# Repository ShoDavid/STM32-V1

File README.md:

# **STM32 - KANA 01**
PCB design using the STM32F103, with SWD programming ports, I2C and UART ports, reset and boot button. With USB port for power and communication.
All master files and manufacturing files you can find in this repository, the idea of this PCB is the result of the tutorial available on Youtube of Phil's Lab (https://www.youtube.com/watch?v=aVUqaB0IMh4)

# Manufacturing
I sent it to manufacture using JLCPCB, I'm using this configuration:

# BOM Using InteractiveHtmlBom 

# After manufacture

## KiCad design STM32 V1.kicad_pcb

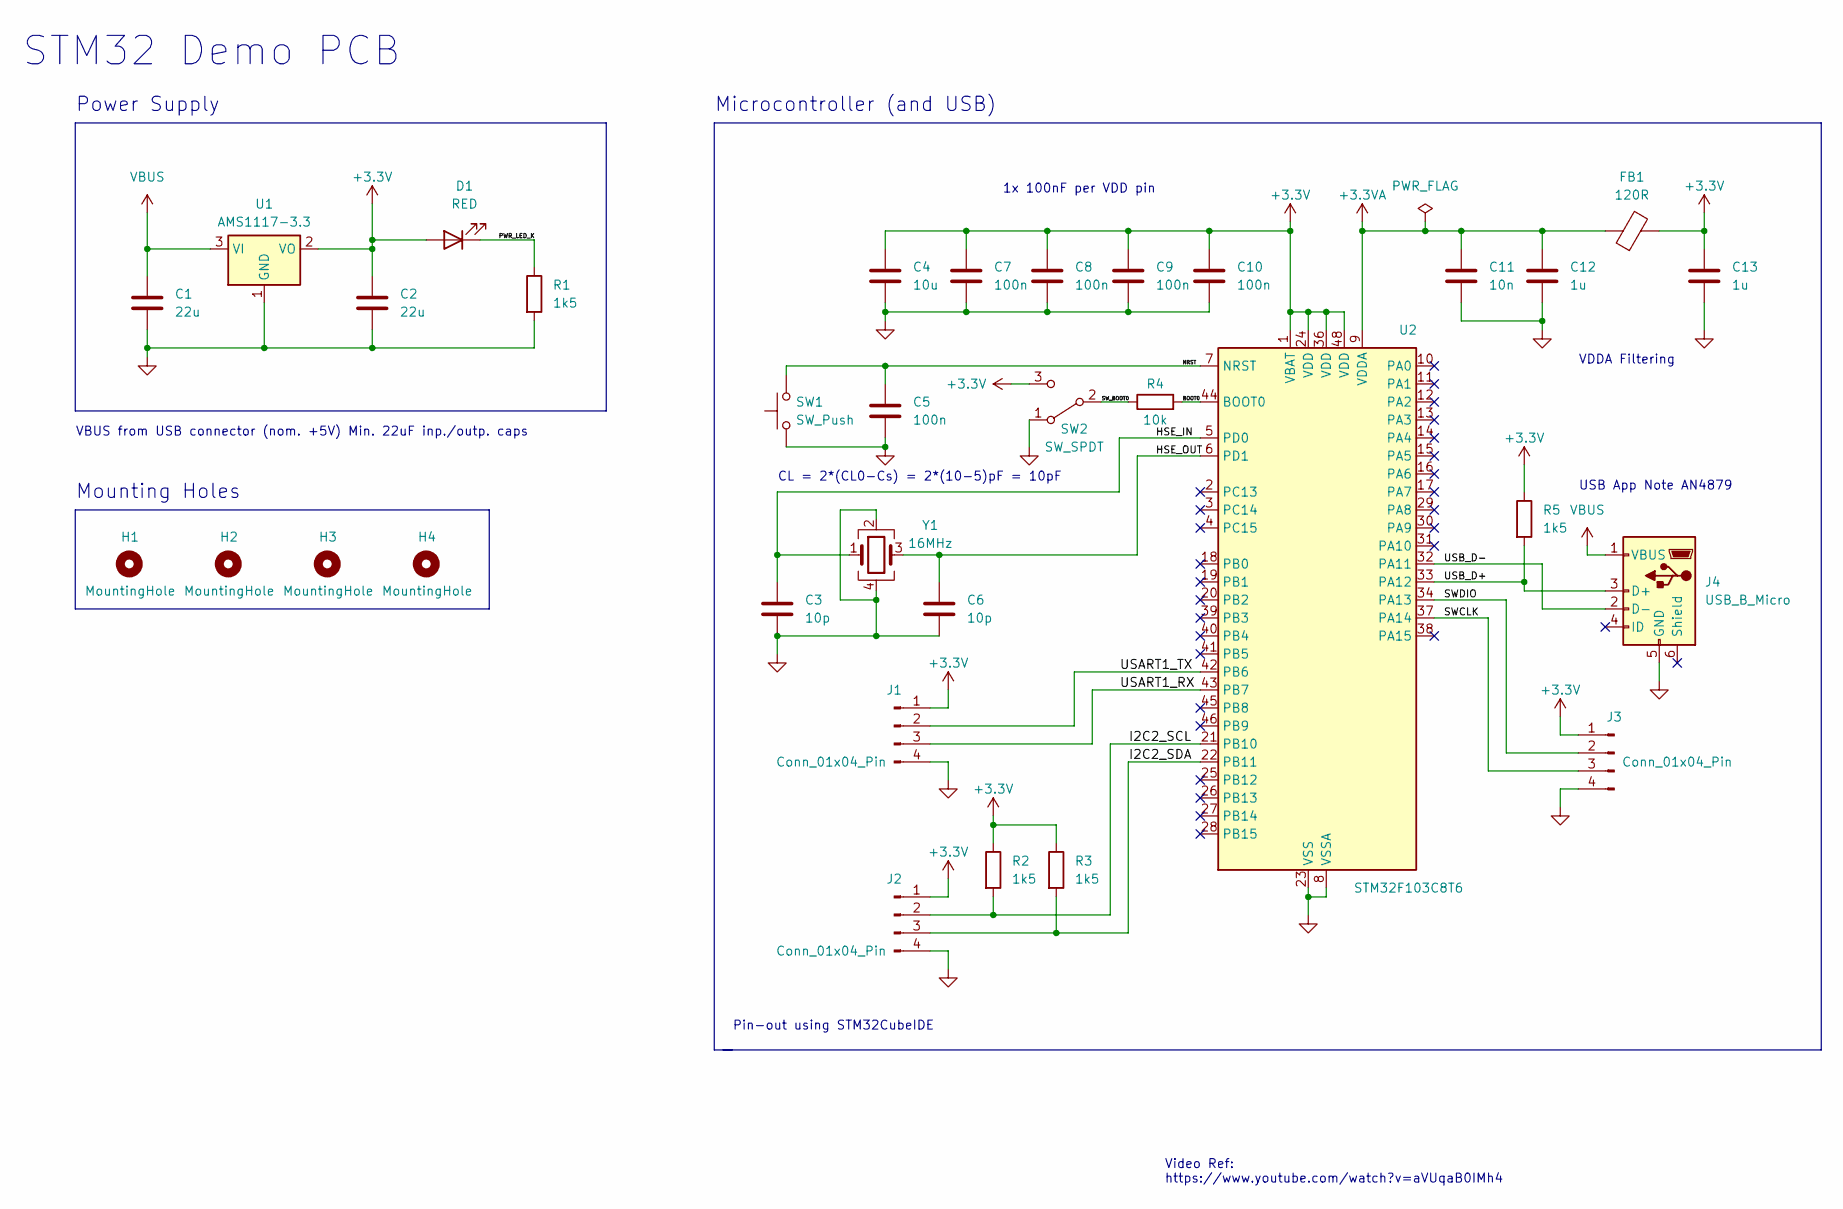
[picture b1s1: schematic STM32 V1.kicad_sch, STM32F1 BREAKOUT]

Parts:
C1, C2: 22u; C_0805_2012Metric
C3, C6: 10p; C_0402_1005Metric
C4: 10u; C_0603_1608Metric
C5, C7, C8, C9, C10: 100n; C_0402_1005Metric
C11: 10n; C_0402_1005Metric
C12, C13: 1u; C_0402_1005Metric
D1: RED; LED_0603_1608Metric
FB1: 120R; L_0603_1608Metric
H1, H2, H3, H4: MountingHole; MountingHole_2.2mm_M2
J1, J2, J3: Conn_01x04_Pin; PinHeader_1x04_P2.54mm_Vertical
J4: USB_B_Micro; USB_Micro-B_Wuerth_629105150521
R1, R2, R3, R5: 1k5; R_0402_1005Metric
R4: 10k; R_0402_1005Metric
SW1: SW_Push; SW_SPST_PTS645
SW2: SW_SPDT; SW_SPDT_PCM12
U1: AMS1117-3.3; SOT-223-3_TabPin2
U2: STM32F103C8T6; LQFP-48_7x7mm_P0.5mm
Y1: 16MHz; Crystal_SMD_3225-4Pin_3.2x2.5mm

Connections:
+3.3V: C2.1, C4.1, C7.1, C8.1, C9.1, C10.1, C13.1, D1.2 (A), FB1.2, J1.1, J2.1, J3.1, R2.1, R3.1, R5.1, SW2.3 (C), U1.2 (VO), U2.1 (VBAT), U2.24 (VDD), U2.36 (VDD), U2.48 (VDD)
+3.3VA: C11.1, C12.1, FB1.1, U2.9 (VDDA)
/BOOT0: R4.2, U2.44 (BOOT0)
/HSE_IN: C3.1, U2.5 (PD0), Y1.1
/HSE_OUT: C6.1, U2.6 (PD1), Y1.3
/I2C2_SCL: J2.2, R2.2, U2.21 (PB10)
/I2C2_SDA: J2.3, R3.2, U2.22 (PB11)
/NRST: C5.1, SW1.2, U2.7 (NRST)
/PWR_LED_K: D1.1 (K), R1.1
/SWCLK: J3.3, U2.37 (PA14)
/SWDIO: J3.2, U2.34 (PA13)
/SW_BOOT0: R4.1, SW2.2 (B)
/USART1_RX: J1.3, U2.43 (PB7)
/USART1_TX: J1.2, U2.42 (PB6)
/USB_D+: J4.3 (D+), R5.2, U2.33 (PA12)
/USB_D-: J4.2 (D-), U2.32 (PA11)
GND: C1.2, C2.2, C3.2, C4.2, C5.2, C6.2, C7.2, C8.2, C9.2, C10.2, C11.2, C12.2, C13.2, J1.4, J2.4, J3.4, J4.5 (GND), R1.2, SW1.1, SW2.1 (A), U1.1 (GND), U2.8 (VSSA), U2.23 (VSS), U2.35 (VSS), U2.47 (VSS), Y1.2, Y1.4
VBUS: C1.1, J4.1 (VBUS), U1.3 (VI)

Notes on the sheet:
VDDA Filtering
Pin-out using STM32CubeIDE
Video Ref: https://www.youtube.com/watch?v=aVUqaB0IMh4
VBUS from USB connector (nom. +5V) Min. 22uF inp./outp. caps
Microcontroller (and USB)
Mounting Holes
CL = 2*(CL0-Cs) = 2*(10-5)pF = 10pF
USB App Note AN4879
Power Supply
1x 100nF per VDD pin
STM32 Demo PCB

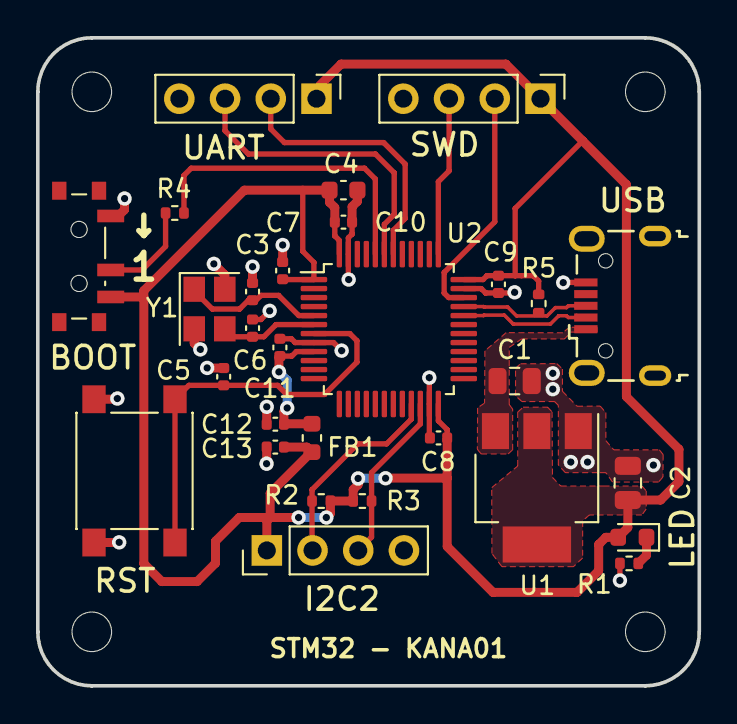
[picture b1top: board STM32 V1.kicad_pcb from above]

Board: 2 copper layers, 36.8 x 36.0 mm, 33 parts (0 on the bottom side), 18 nets.

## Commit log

2023-12-31 Add files via upload
    Interactive BOM using Interactive HTML BOM plugin for KiCad.
2023-12-31 Add files via upload
    Manufacturing files, you can download this file and sent it to manufacturer!
2023-12-31 Add files via upload
    Master files - KiCad 7
